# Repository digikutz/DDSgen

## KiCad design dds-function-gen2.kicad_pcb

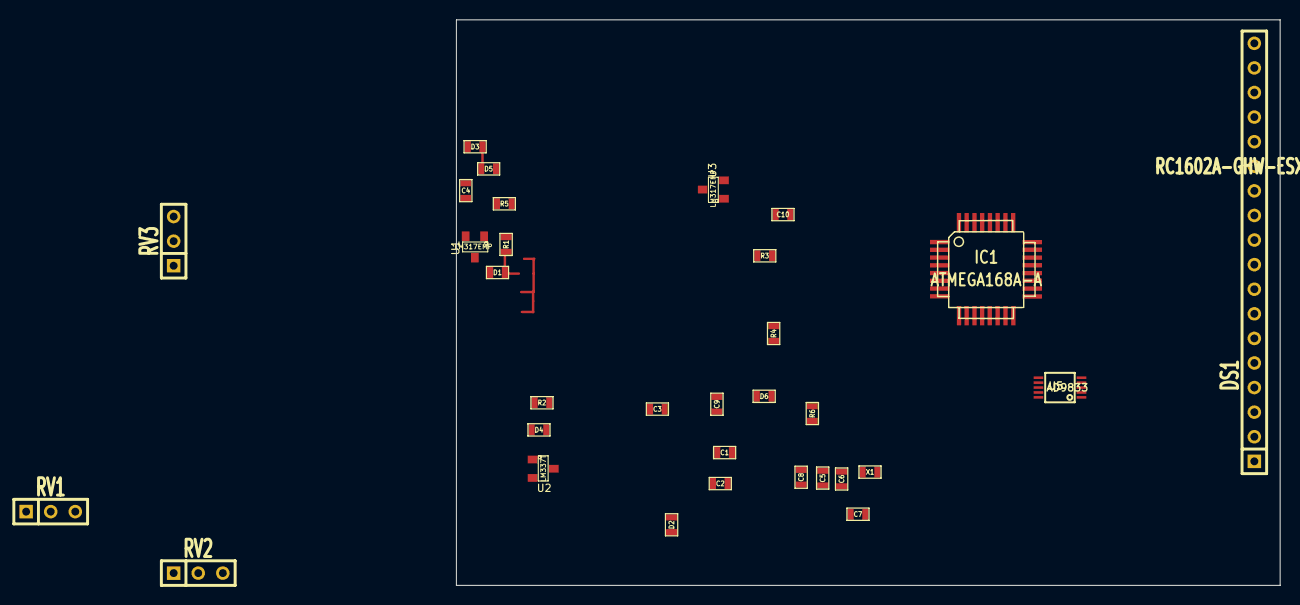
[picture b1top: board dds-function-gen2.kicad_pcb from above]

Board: 2 copper layers, 85.1 x 58.4 mm, 32 parts (0 on the bottom side), 21 nets.

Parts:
C1, C2, C3, C4, C5: CP1; SM0603
C6, C7: 18pF; SM0603
C8, C9, C10: 0.01uF; SM0603
D1, D2, D3, D4, D5, D6: DIODE; SM0603
DS1: RC1602A-GHW-ESX; SIL-18
IC1: ATMEGA168A-A; TQFP32
R1, R2, R3, R4, R5, R6: R; SM0603
RV1, RV2, RV3: POT; SIL-3
U1, U3: LM317EMP; SOT23
U2: LM337T; SOT23
U5: AD9833; MSOP10-0.5
X1: 20Mhz; SM0603

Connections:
+5VD: C5.1, C8.2, C9.2, C10.2, D5.1, D6.2, DS1.2, DS1.3, DS1.15, IC1.4, IC1.6, IC1.18, R3.1, R4.1, R5.1, R6.1, U3.2, U5.2, U5.3
+12V: C3.1, D1.1, D3.2, D5.2, R1.1, U1.2, U3.3
-12V: C4.2, D4.1, R2.2, U2.3
AGND: C1.2, C2.1, C3.2, C4.1, C5.2, C6.2, C7.2, C8.1, C9.1, DS1.1, DS1.5, DS1.16, IC1.3, IC1.5, IC1.21, RV1.3, RV2.1, RV3.3, U5.4, U5.9
FSYNC: IC1.15, R6.2, U5.8
unnamed: C10.1, U5.1
unnamed: C6.1, IC1.7, X1.2
unnamed: C7.1, IC1.8, X1.1
unnamed: C2.2, U2.2
unnamed: C1.1, D1.2, U1.3
unnamed: D4.2, R2.1, RV2.2, RV2.3, U2.1
unnamed: D6.1, R3.2, RV3.1, RV3.2, U3.1
unnamed: D3.1, R1.2, RV1.1, RV1.2, U1.1
PC0: DS1.11, IC1.23
PC1: DS1.12, IC1.24
PC2: DS1.13, IC1.25
PC3: DS1.14, IC1.26
PC4: DS1.4, IC1.27
PC5: DS1.6, IC1.28
SCLK: IC1.17, R4.2, U5.7
SDATA: IC1.16, R5.2, U5.6

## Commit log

2014-03-07 Initial Design POC
2014-04-11 PCB's in progress
